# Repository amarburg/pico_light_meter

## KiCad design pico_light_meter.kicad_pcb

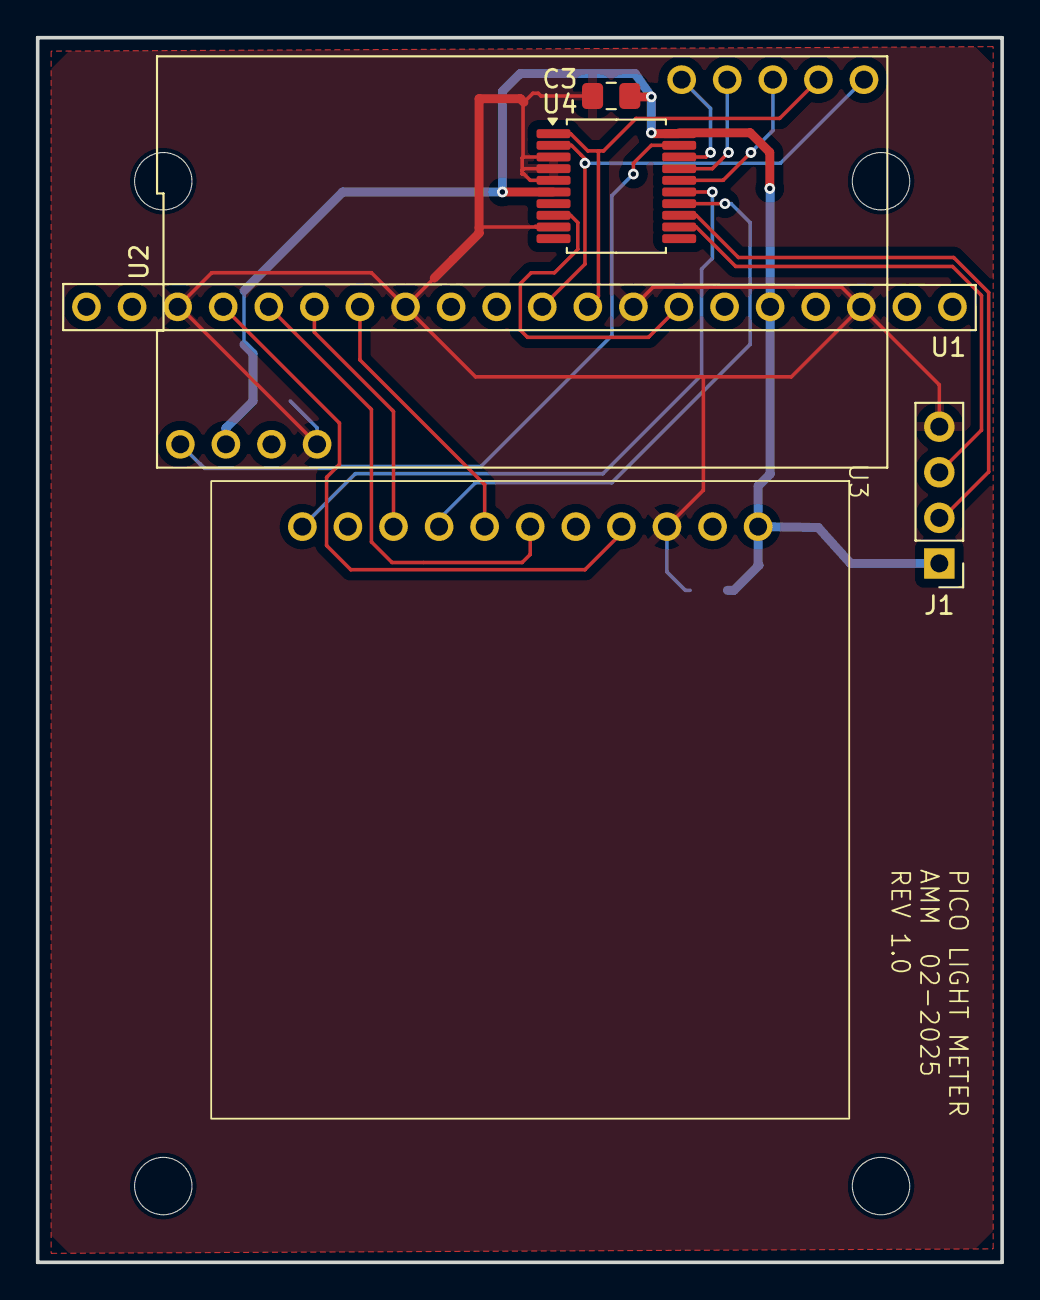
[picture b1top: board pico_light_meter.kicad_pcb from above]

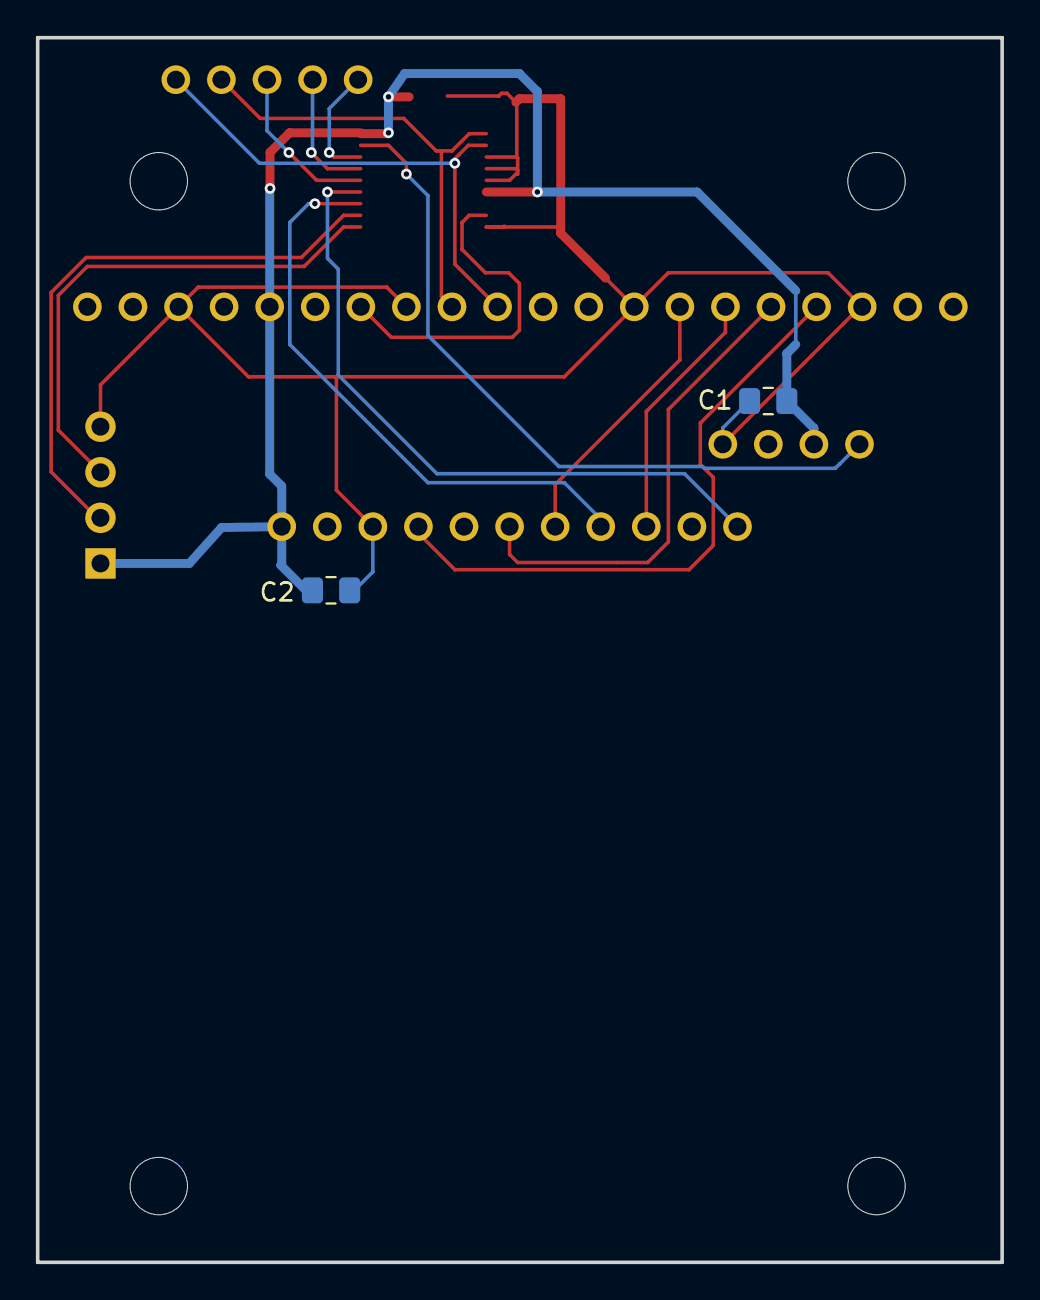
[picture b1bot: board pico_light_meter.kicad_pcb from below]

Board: 2 copper layers, 53.8 x 68.2 mm, 12 parts (2 on the bottom side), 17 nets.

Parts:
C1, C2, C3: C; C_0805_2012Metric_Pad1.18x1.45mm_HandSolder
H1, H2, H3, H4: MountingHole; MountingHole_3.2mm_M3_ISO14580
J1: Conn_01x04; PinHeader_1x04_P2.54mm_Vertical
U1: pico2_right_pins_only
U2: feather
U3: adafruit_2.0_IPS_Display_minimal
U4: MCP23008-xSS; SSOP-20_5.3x7.2mm_P0.65mm

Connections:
+3.3V: C1.1, C2.1, C3.1, J1.1, U1.36 (3v3), U2.2 (3v3), U3.11 (VIN), U4.6 (~RESET), U4.20 (VDD)
/I2C1_SCL: U1.32 (GPIO27/AD1), U2.18 (SCL), U4.1 (SCL)
/I2C1_SDA: U1.31 (GPIO26/AD0), U2.17 (SDA), U4.2 (SDA)
/IPS_BACKLIGHT: U3.1 (BACKLIGHT), U4.15 (GP3)
/IPS_CS: U1.27 (GPIO21), U3.5 (TFT_CS)
/IPS_DC: U1.26 (GPIO20), U3.3 (TFT_DC)
/IPS_MOSI: U1.25 (_MOSI), U3.6 (MOSI)
/IPS_RESET: U3.4 (RESET), U4.14 (GP2)
/IPS_SCK: U1.24 (_SCK), U3.8 (SCLK)
/MCP_INT: U1.34 (GPIO2/AD2), U4.8 (INT)
/SW2: U2.21 (SW2), U4.18 (GP6)
/SW3: U2.19 (SW3), U4.16 (GP4)
/SW4: U2.20 (SW4), U4.17 (GP5)
/SW5: U2.1 (/RESET), U4.19 (GP7)
GND: C1.2, C2.2, C3.2, J1.4, U1.23 (GND), U1.28 (GND), U1.33 (GND), U1.38 (GND), U2.4 (GND), U3.9 (GND), U4.3 (A2), U4.4 (A1), U4.5 (A0), U4.9 (VSS)
unnamed: J1.2, U4.13 (GP1)
unnamed: J1.3, U4.12 (GP0)

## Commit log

2025-01-25 Intermediate commit of routed board with Pico on top.
2025-01-25 Another iteration, now with Pico on bottom
2025-01-27 Updated with MCP port expander
2025-01-28 Big update to board
